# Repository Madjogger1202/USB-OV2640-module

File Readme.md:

# USB-OV2640-module  

> Compact USB camera module based on **ESP32-S3** with directly soldered **OV2640** sensor (BGA footprint).  
> Conceptually close to ESP32-CAM, but implemented in a **USB stick form factor** with integrated antenna and memory.  
> Designed as a flexible platform that can later be adapted to other sensors and microcontrollers.  

---

## What’s on the board  
- **ESP32-S3 microcontroller**  
>  - Native **DVP camera interface** for OV2640  
>  - USB 2.0 device controller (Type-C connector)  
- **OV2640 camera sensor** in BGA package (soldered directly)  
>  - Data lines matched in length with pixel clock  
>  - Pin mapping (see table below)  
- **External memories**:  
>  - **W25Q64JVSSIQ** (SPI NOR Flash, 64 Mbit)  
>  - **LY68L6400SLIT** (PSRAM, 64 Mbit)  
- **PCB antenna**
>  - LC matching network (tunable if needed)  
- **Power & protection**:  
>  - ESD protection on USB data and power  
>  - Small differential USB filter  
- **Debug & programming**:  
>  - BOOT and RESET buttons  
>  - UART broken out for flashing/debug  
>  - Extra GPIOs exposed (see table below)  
>  - JTAG pads (MTCK, MTDO, MTDI, MTMS) 

---

## Pinout (ESP32-S3 ↔ OV2640)  

| ESP32-S3 GPIO | OV2640 Signal | Notes |
|---------------|---------------|-------|
| GPIO1  | Y9    | Data bus |
| GPIO2  | Y8    | Data bus |
| GPIO3  | Y7    | Data bus |
| GPIO4  | Y6    | Data bus |
| GPIO5  | Y5    | Data bus |
| GPIO6  | Y4    | Data bus |
| GPIO7  | Y3    | Data bus |
| GPIO8  | Y2    | Data bus |
| GPIO9  | PCLK  | Pixel clock |
| GPIO10 | XVCLK | External clock |
| GPIO11 | HREF  | Horizontal reference |
| GPIO12 | VSYNC | Vertical sync |
| GPIO13 | RESETB | Sensor reset |
| GPIO18 | SIO_C | SCCB/I²C clock |
| GPIO17 | SIO_D | SCCB/I²C data |
| GPIO14 | STROBE | Camera strobe |
| GPIO38 | FREX   | Frame exposure |
| GPIO37 | EXPST_B | Exposure start |

---

## Extra Exposed GPIOs  

| GPIO   | Possible Functions (ESP32-S3 datasheet) |
|--------|-----------------------------------------|
| GPIO33 | ADC1_CH2 • Touch5 • RMT • SPI • UART • PWM |
| GPIO34 | ADC1_CH3 • Touch6 • RMT • SPI • UART • PWM |
| GPIO35 | ADC1_CH4 • Touch7 • RMT • SPI • UART • PWM |
| GPIO36 | ADC1_CH5 • Touch8 • RMT • SPI • UART • PWM |
| GPIO45 | General-purpose IO (no ADC/touch) • HSPI/VSPI • PWM • UART |
| GPIO46 | Input-only • Strapping pin • Can be used as input for boot mode, JTAG, etc. |
| GPIO21 | ADC2_CH0 • Touch0 • I²C SDA • UART • PWM |
| GPIO15 | ADC2_CH4 • Touch3 • I²C SCL • UART • PWM |
| GPIO16 | ADC2_CH5 • Touch4 • SPI • UART • PWM |

*Notes:*  
>- **ADC1** and **ADC2** allow analog measurements (12-bit).  
>- **TouchX** functions support capacitive touch sensing.  
>- **RMT** = Remote Control peripheral (good for IR / precise waveforms).  
>- GPIO45/46 often used in special boot/JTAG scenarios — check strapping requirements.  
>- All can be remapped to **UART / I²C / SPI / PWM** as needed (ESP32-S3 flexible IO matrix).  

---

## Power & Form Factor  
>- Powered directly from **USB Type-C**  
>- Compact **2-layer PCB** for low-cost manufacturing  
>- No external power required  

---

## Use Case  
>- Drop-in USB camera module with OV2640 sensor  
>- Alternative to ESP32-CAM with direct USB interface  
>- For prototyping, computer vision, robotics, and IoT devices  

---

## Quick Use  
>1. Connect **USB-OV2640-module** to PC via USB-C.  
>2. Hold **BOOT** and press **RESET** to enter download mode.  
>3. Flash ESP32-S3 firmware (e.g. ESP-IDF / Arduino / PlatformIO).  
>4. Use provided OV2640 driver examples (similar to ESP32-CAM).  
>5. Stream video over USB (UVC emulation) or Wi-Fi.  

---

## Notes  
>- Antenna may require LC matching calibration depending on PCB batch.  
>- OV2640 mounted directly in BGA footprint (reflow soldering required).  
>- Camera lines length-matched for stable operation at full pixel clock.  
>- PCB made as **2-layer** design for cost efficiency.  

---

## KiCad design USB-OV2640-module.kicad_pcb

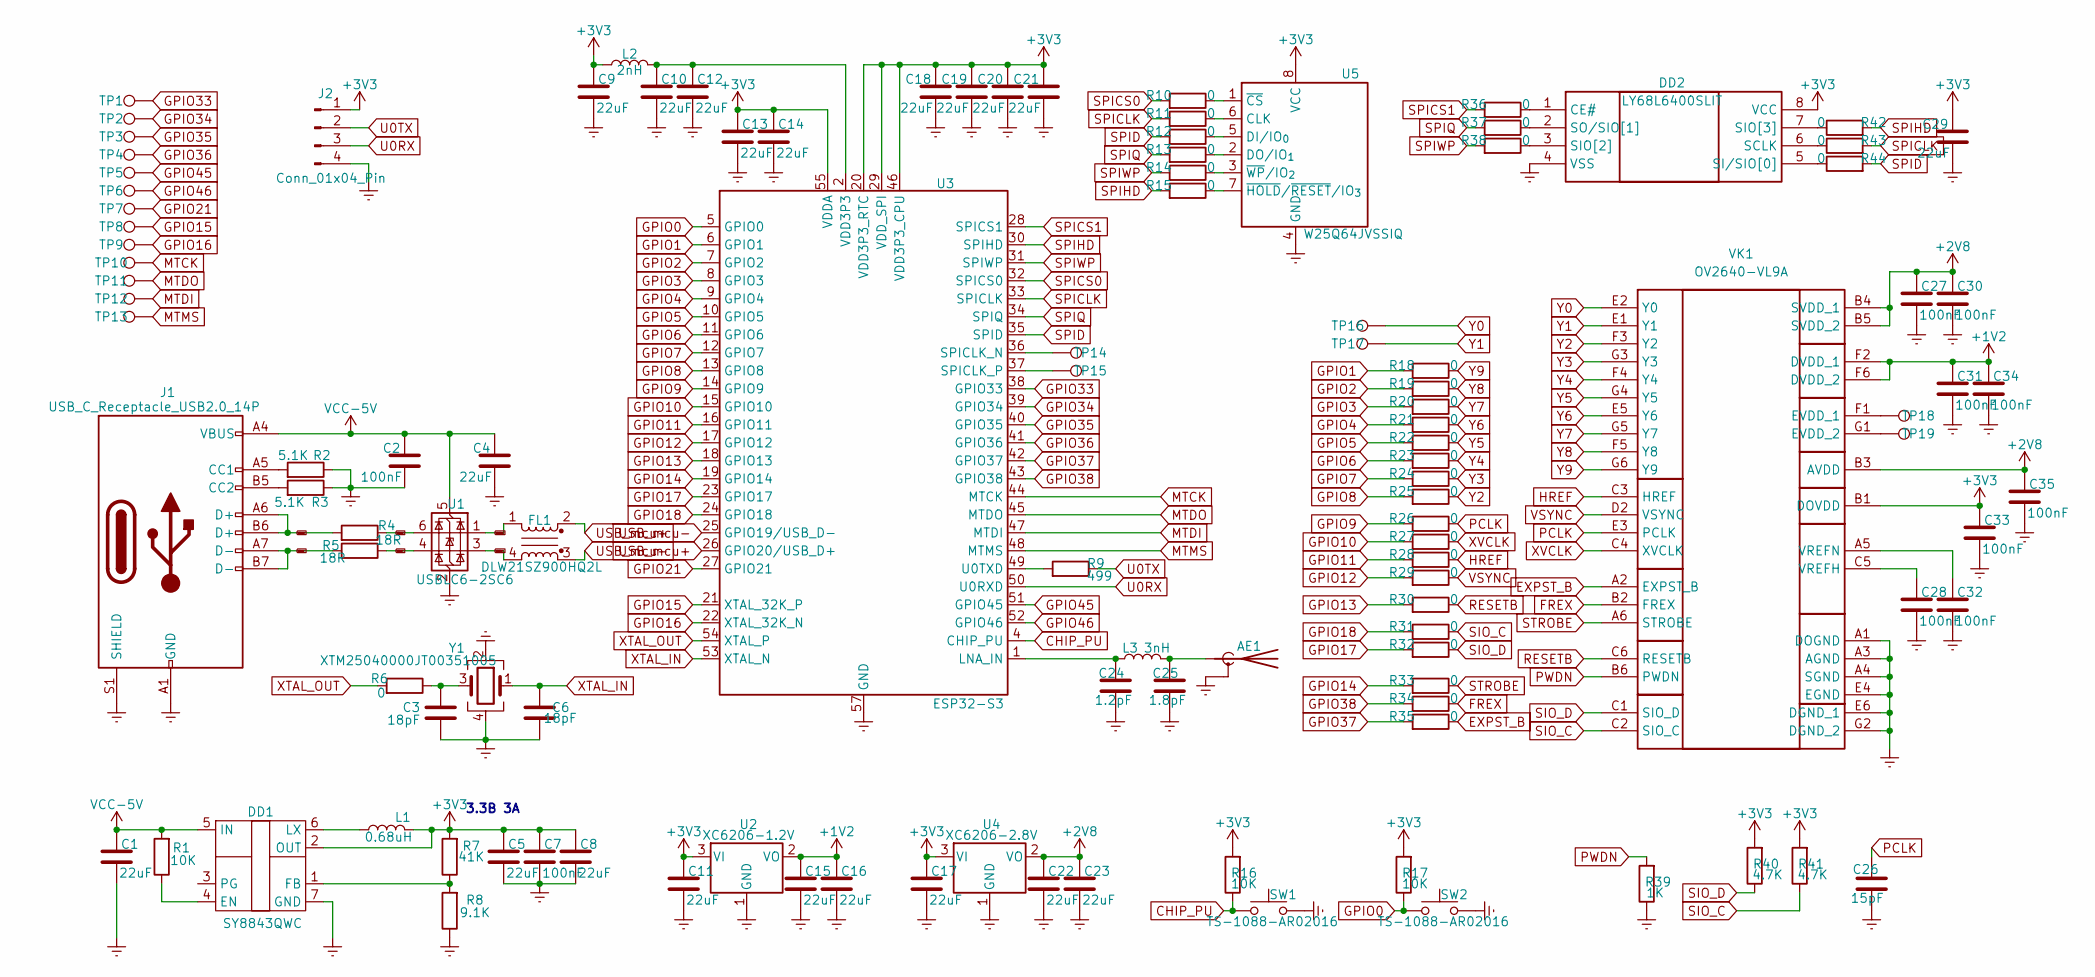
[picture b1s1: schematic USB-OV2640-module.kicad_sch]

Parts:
AE1: Antenna_Shield; Texas_SWRA117D_2.4GHz_Left
C1, C4, C5, C8, C9, C10, C11, C12, C13, C14, C15, C16, C17, C18, C19, C20, C21, C22, C23, C29: 22uF; C_0402_1005Metric
C2, C7, C27, C28, C30, C31, C32, C33, C34, C35: 100nF; C_0402_1005Metric
C3, C6: 18pF; C_0603_1608Metric
C24: 1.2pF; C_0201_0603Metric
C25: 1.8pF; C_0201_0603Metric
C26: 15pF; C_0402_1005Metric
DD1: SY8843QWC
DD2: LY68L6400SLIT; Manufacturer_Part_Number LY68L6400SLIT
FL1: DLW21SZ900HQ2L; L_CommonModeChoke_Coilcraft_0805USB
J1: USB_C_Receptacle_USB2.0_14P; USB_C_Receptacle_GCT_USB4105-xx-A_16P_TopMnt_Horizontal
J2: Conn_01x04_Pin; PinSocket_1x04_P2.54mm_Vertical
L1: 0.68uH; L_Cenker_CKCS4020
L2: 2nH; L_0402_1005Metric
L3: 3nH; L_0201_0603Metric
R1, R16, R17: 10K; R_0402_1005Metric
R2, R3: 5.1K; R_0402_1005Metric
R4, R5: 18R; R_0402_1005Metric
R6, R10, R11, R12, R13, R14, R15, R18, R19, R20, R21, R22, R23, R24, R25, R26, R27, R28, R29, R30, R31, R32, R33, R34, R35, R36, R37, R38, R42, R43, R44: 0; R_0402_1005Metric
R7: 41К; R_0402_1005Metric
R8: 9.1K; R_0402_1005Metric
R9: 499; R_0402_1005Metric
R39: 1K; R_0402_1005Metric
R40, R41: 4.7K; R_0402_1005Metric
SW1, SW2: TS-1088-AR02016; SW_SPST_B3U-1000P
TP1, TP2, TP3, TP4, TP5, TP6, TP7, TP8, TP9, TP10, TP11, TP12, TP13, TP14, TP15, TP16, TP17, TP18, TP19: TestPoint; TestPoint_Pad_D1.0mm
U1: USBLC6-2SC6; SOT-23-6
U2: XC6206-1.2V; SOT-23-3
U3: ESP32-S3; QFN-56-1EP_7x7mm_P0.4mm_EP4x4mm
U4: XC6206-2.8V; SOT-23-3
U5: W25Q64JVSSIQ; SOIC-8_5.3x5.3mm_P1.27mm
VK1: OV2640-VL9A; OV2640; Manufacturer_Part_Number OV2640-VL9A
Y1: XTM25040000JT00351005; Crystal_SMD_2520-4Pin_2.5x2.0mm

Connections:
+1V2: C15.1, C16.1, C31.1, C34.1, U2.2 (VO), VK1.F2 (DVDD_1), VK1.F6 (DVDD_2)
+2V8: C22.1, C23.1, C27.1, C30.1, C35.1, U4.2 (VO), VK1.B3 (AVDD), VK1.B4 (SVDD_1), VK1.B5 (SVDD_2)
+3V3: C5.1, C7.1, C8.1, C9.1, C11.1, C13.1, C14.1, C17.1, C18.1, C19.1, C20.1, C21.1, C29.1, C33.1, DD1.2 (OUT), DD2.8 (VCC), J2.1, L1.2, L2.1, R7.2, R16.2, R17.2, R40.2, R41.2, U2.3 (VI), U3.20 (VDD3P3_RTC), U3.29 (VDD_SPI), U3.46 (VDD3P3_CPU), U3.55 (VDDA), U3.56 (VDDA), U4.3 (VI), U5.8 (VCC), VK1.B1 (DOVDD)
CHIP_PU: R16.1, SW1.1, U3.4 (CHIP_PU); also elsewhere on the board
EXPST_B: R35.1, VK1.A2 (EXPST_B)
Earth: AE1.2 (Shield), C1.2, C2.2, C3.1, C4.2, C5.2, C6.1, C7.2, C8.2, C9.2, C10.2, C11.2, C12.2, C13.2, C14.2, C15.2, C16.2, C17.2, C18.2, C19.2, C20.2, C21.2, C22.2, C23.2, C24.2, C25.2, C26.2, C27.2, C28.2, C29.2, C30.2, C31.2, C32.2, C33.2, C34.2, C35.2, DD1.7 (GND), DD2.4 (VSS), J1.A1 (GND), J1.A12 (GND), J1.B1 (GND), J1.B12 (GND), J1.S1 (SHIELD), J2.4, R2.1, R3.1, R8.1, R39.1, SW1.2, SW2.2, U1.2 (GND), U2.1 (GND), U3.57 (GND), U4.1 (GND), U5.4 (GND), VK1.A1 (DOGND), VK1.A3 (AGND), VK1.A4 (SGND), VK1.E4 (EGND), VK1.E6 (DGND_1), VK1.G2 (DGND_2), Y1.2, Y1.4; also elsewhere on the board
FREX: R34.1, VK1.B2 (FREX)
GPIO0: R17.1, SW2.1, U3.5 (GPIO0); also elsewhere on the board
GPIO1: R18.2, U3.6 (GPIO1)
GPIO2: R19.2, U3.7 (GPIO2)
GPIO3: R20.2, U3.8 (GPIO3)
GPIO4: R21.2, U3.9 (GPIO4)
GPIO5: R22.2, U3.10 (GPIO5)
GPIO6: R23.2, U3.11 (GPIO6)
GPIO7: R24.2, U3.12 (GPIO7)
GPIO8: R25.2, U3.13 (GPIO8)
GPIO9: R26.2, U3.14 (GPIO9)
GPIO10: R27.2, U3.15 (GPIO10)
GPIO11: R28.2, U3.16 (GPIO11)
GPIO12: R29.2, U3.17 (GPIO12)
GPIO13: R30.2, U3.18 (GPIO13)
GPIO14: R33.2, U3.19 (GPIO14)
GPIO15: TP8.1, U3.21 (XTAL_32K_P)
GPIO16: TP9.1, U3.22 (XTAL_32K_N)
GPIO17: R32.2, U3.23 (GPIO17)
GPIO18: R31.2, U3.24 (GPIO18)
GPIO21: TP7.1, U3.27 (GPIO21)
GPIO33: TP1.1, U3.38 (GPIO33)
GPIO34: TP2.1, U3.39 (GPIO34)
GPIO35: TP3.1, U3.40 (GPIO35)
GPIO36: TP4.1, U3.41 (GPIO36)
GPIO37: R35.2, U3.42 (GPIO37)
GPIO38: R34.2, U3.43 (GPIO38)
GPIO45: TP5.1, U3.51 (GPIO45)
GPIO46: TP6.1, U3.52 (GPIO46)
HREF: R28.1, VK1.C3 (HREF)
MTCK: TP10.1, U3.44 (MTCK)
MTDI: TP12.1, U3.47 (MTDI)
MTDO: TP11.1, U3.45 (MTDO)
MTMS: TP13.1, U3.48 (MTMS)
unnamed: AE1.1 (A), C25.1, L3.2
unnamed: C3.2, R6.1, Y1.3
unnamed: C10.1, C12.1, L2.2, U3.2 (VDD3P3), U3.3 (VDD3P3)
unnamed: DD1.4 (EN), R1.1
unnamed: DD1.1 (FB), R7.1, R8.2
unnamed: DD1.6 (LX), L1.1
unnamed: DD2.1 (CE#), R36.1
unnamed: DD2.6 (SCLK), R43.1
unnamed: DD2.3 (SIO[2]), R38.1
unnamed: DD2.7 (SIO[3]), R42.1
unnamed: DD2.5 (SI/SIO[0]), R44.1
unnamed: DD2.2 (SO/SIO[1]), R37.1
unnamed: J1.A5 (CC1), R2.2
unnamed: J1.B5 (CC2), R3.2
unnamed: C24.1, L3.1, U3.1 (LNA_IN)
unnamed: TP14.1, U3.36 (SPICLK_N)
unnamed: TP15.1, U3.37 (SPICLK_P)
unnamed: R9.2, U3.49 (U0TXD)
unnamed: R11.1, U5.6 (CLK)
unnamed: R12.1, U5.5 (DI/IO_{0})
unnamed: R13.1, U5.2 (DO/IO_{1})
unnamed: R10.1, U5.1 (~CS)
unnamed: R15.1, U5.7 (~HOLD/~RESET/IO_{3})
unnamed: R14.1, U5.3 (~WP/IO_{2})
unnamed: TP18.1, VK1.F1 (EVDD_1)
unnamed: TP19.1, VK1.G1 (EVDD_2)
unnamed: C28.1, VK1.C5 (VREFH)
unnamed: C32.1, VK1.A5 (VREFN)
PCLK: C26.1, R26.1, VK1.E3 (PCLK)
PWDN: R39.2, VK1.B6 (PWDN)
RESETB: R30.1, VK1.C6 (RESETB)
SIO_C: R31.1, R41.1, VK1.C2 (SIO_C)
SIO_D: R32.1, R40.1, VK1.C1 (SIO_D)
SPICLK: R11.2, R43.2, U3.33 (SPICLK)
SPICS0: R10.2, U3.32 (SPICS0)
SPICS1: R36.2, U3.28 (SPICS1)
SPID: R12.2, R44.2, U3.35 (SPID)
SPIHD: R15.2, R42.2, U3.30 (SPIHD)
SPIQ: R13.2, R37.2, U3.34 (SPIQ)
SPIWP: R14.2, R38.2, U3.31 (SPIWP)
STROBE: R33.1, VK1.A6 (STROBE)
U0RX: J2.3, U3.50 (U0RXD)
U0TX: J2.2, R9.1
USB_con+: J1.A6 (D+), J1.B6 (D+), R4.2
USB_con-: J1.A7 (D-), J1.B7 (D-), R5.2
USB_filter+: FL1.1, U1.1 (I/O1)
USB_filter-: FL1.4, U1.3 (I/O2)
USB_mcu+: FL1.2, U3.26 (GPIO20/USB_D+)
USB_mcu-: FL1.3, U3.25 (GPIO19/USB_D-)
USB_res+: R4.1, U1.6 (I/O1)
USB_res-: R5.1, U1.4 (I/O2)
VCC-5V: C1.1, C2.1, C4.1, DD1.5 (IN), J1.A4 (VBUS), J1.A9 (VBUS), J1.B4 (VBUS), J1.B9 (VBUS), R1.2, U1.5 (VBUS)
VSYNC: R29.1, VK1.D2 (VSYNC)
XTAL_IN: C6.2, U3.53 (XTAL_N), Y1.1
XTAL_OUT: R6.2, U3.54 (XTAL_P)
XVCLK: R27.1, VK1.C4 (XVCLK)
Y0: TP16.1, VK1.E2 (Y0)
Y1: TP17.1, VK1.E1 (Y1)
Y2: R25.1, VK1.F3 (Y2)
Y3: R24.1, VK1.G3 (Y3)
Y4: R23.1, VK1.F4 (Y4)
Y5: R22.1, VK1.G4 (Y5)
Y6: R21.1, VK1.E5 (Y6)
Y7: R20.1, VK1.G5 (Y7)
Y8: R19.1, VK1.F5 (Y8)
Y9: R18.1, VK1.G6 (Y9)

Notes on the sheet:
3.3В 3А

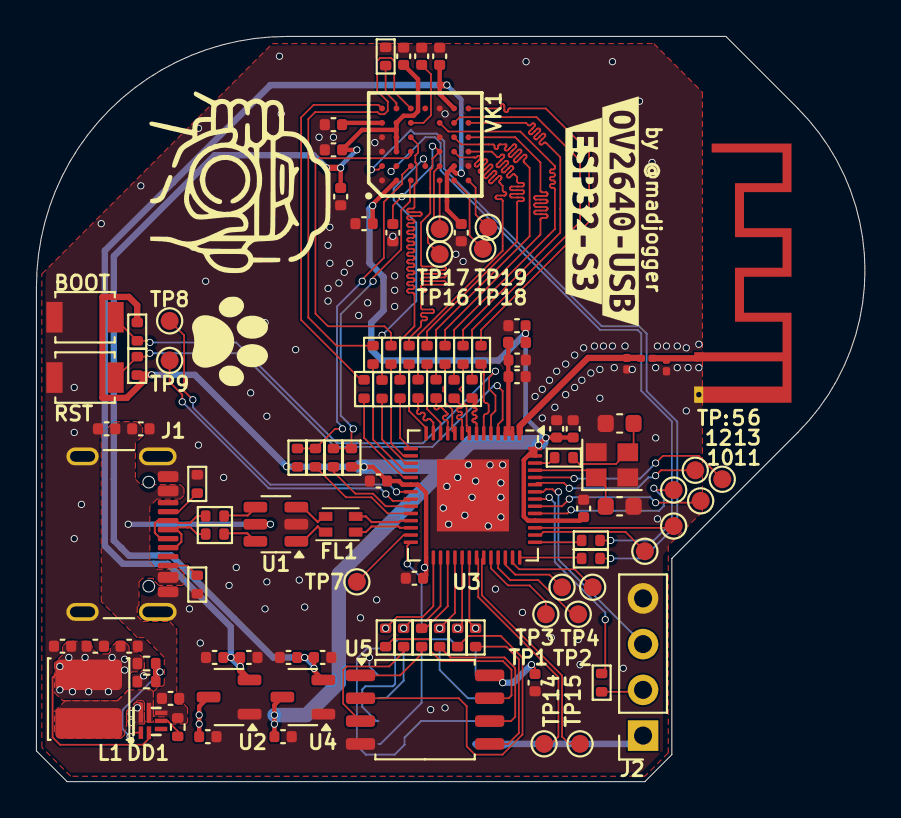
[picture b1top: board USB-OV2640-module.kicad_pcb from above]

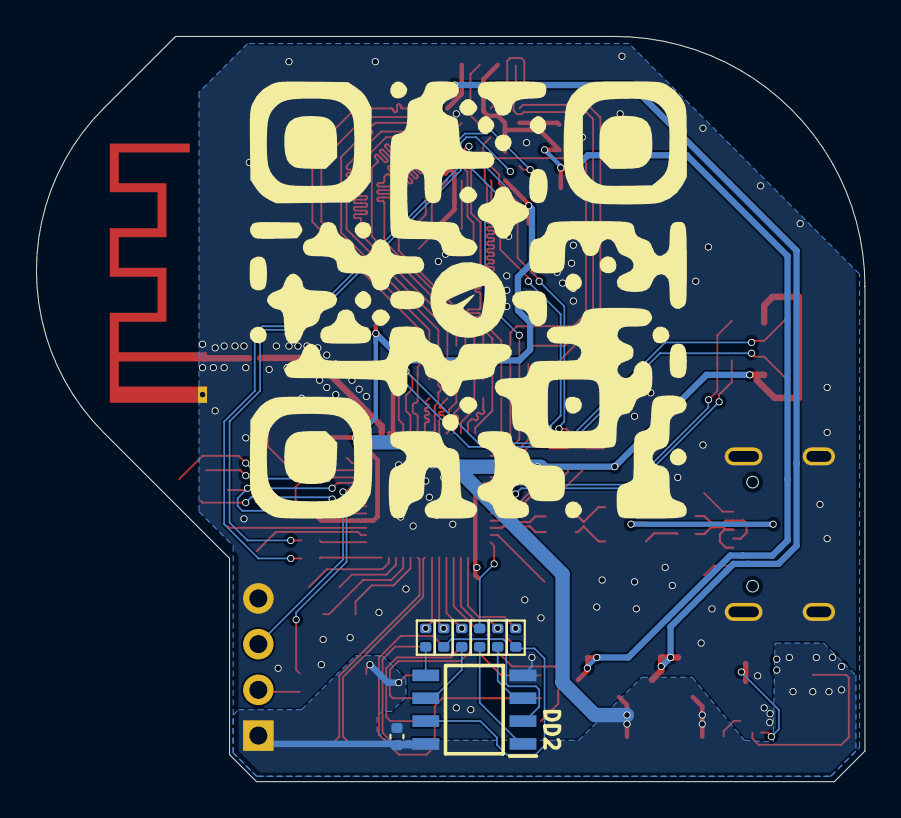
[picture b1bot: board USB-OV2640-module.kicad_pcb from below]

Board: 2 copper layers, 46.0 x 41.4 mm, 118 parts (8 on the bottom side), 106 nets.

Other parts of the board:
BOOT: TS-1088-AR02016; SW_SPST_B3U-1000P
RST: TS-1088-AR02016; SW_SPST_B3U-1000P
kibuzzard-68B606AE: G***; kibuzzard-68B606AE
kibuzzard-68B606C1: G***; kibuzzard-68B606C1

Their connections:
CHIP_PU: RST.1; also elsewhere on the board
Earth: BOOT.2, RST.2; also elsewhere on the board
GPIO0: BOOT.1; also elsewhere on the board

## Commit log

2025-08-31 schematics done
2025-09-01 Rev0 ready
2025-09-02 added README
2025-09-02 README fix
